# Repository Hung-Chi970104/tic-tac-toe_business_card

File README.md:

# Tic-Tac-Toe Business Card

**A playable RP2040 business card with a printed NFC antenna and a minimax computer opponent.**

[PCB layout](#pcb-layout) · [NFC design](#passive-nfc-and-antenna) · [Demos](#see-it-work) · [Schematic](#schematic) · [Design files](#design-files)

## PCB layout

The layout combines a large copper-coil NFC antenna with the game interface and embedded electronics. The **18 game LEDs form nine dual-colour cells**, giving each player one indicator per square; Next and Select buttons provide the controls.

## What I built

- Designed the RP2040 board, LED interface, USB-C connection and passive NFC circuit.
- Integrated a **25 × 48 mm PCB copper-coil antenna** with an **NT3H2111 NFC tag**.
- Implemented two-player gameplay and a **minimax opponent with alpha-beta pruning**, which skips search branches that cannot improve the chosen move.
- Completed two PCB revisions, resolving the initial NFC fault and demonstrating both gameplay and tap-to-open linking.

## Passive NFC and antenna

The coil is part of the PCB copper, connected to the NFC tag's antenna terminals. A compatible phone supplies the field needed for passive **13.56 MHz** NFC reading, so the portfolio link can be read **without USB power**. Gameplay uses the powered RP2040 and LED circuit.

The grid uses 18 LEDs; three additional indicators sit outside the nine game cells.

## See it work

| Demonstration | Watch |
|---|---|
| Two-player game | [Gameplay video](https://youtube.com/shorts/xTpW4rk7Zjw) |
| Computer opponent | [Minimax gameplay](https://youtu.be/wkJYNbXEyfI) |
| Passive NFC | [Phone tap → portfolio link](https://youtube.com/shorts/Xky8sBx_JWE) |

## Schematic

[Full-resolution schematic](assets/schematic.svg) · [KiCad schematic](Tic-tac-toe_Business_Card.kicad_sch)

## 3D views

Original board renders:

| Front | Back |
|---|---|
|  |  |

## Design files

| Resource | Link |
|---|---|
| KiCad project | [Project file](Tic-tac-toe_Business_Card.kicad_pro) |
| Routed board | [PCB source](Tic-tac-toe_Business_Card.kicad_pcb) |
| Copper layers | [Front](assets/Tic-tac-toe_Business_Card-F_Cu.svg) · [Back](assets/Tic-tac-toe_Business_Card-B_Cu.svg) |
| NFC footprint | [25 × 48 mm antenna source](lib/NFC_Tic_Tac_Toe.pretty/25X48MM_NFC_ANTENNA.kicad_mod) |
| Manufacturing exports | [Production files](production/) |

The repository contains the hardware design and demonstration assets. The gameplay implementation is demonstrated in the videos; a complete firmware release is not currently included here.

Designed and built by Hung-Chi Wang.

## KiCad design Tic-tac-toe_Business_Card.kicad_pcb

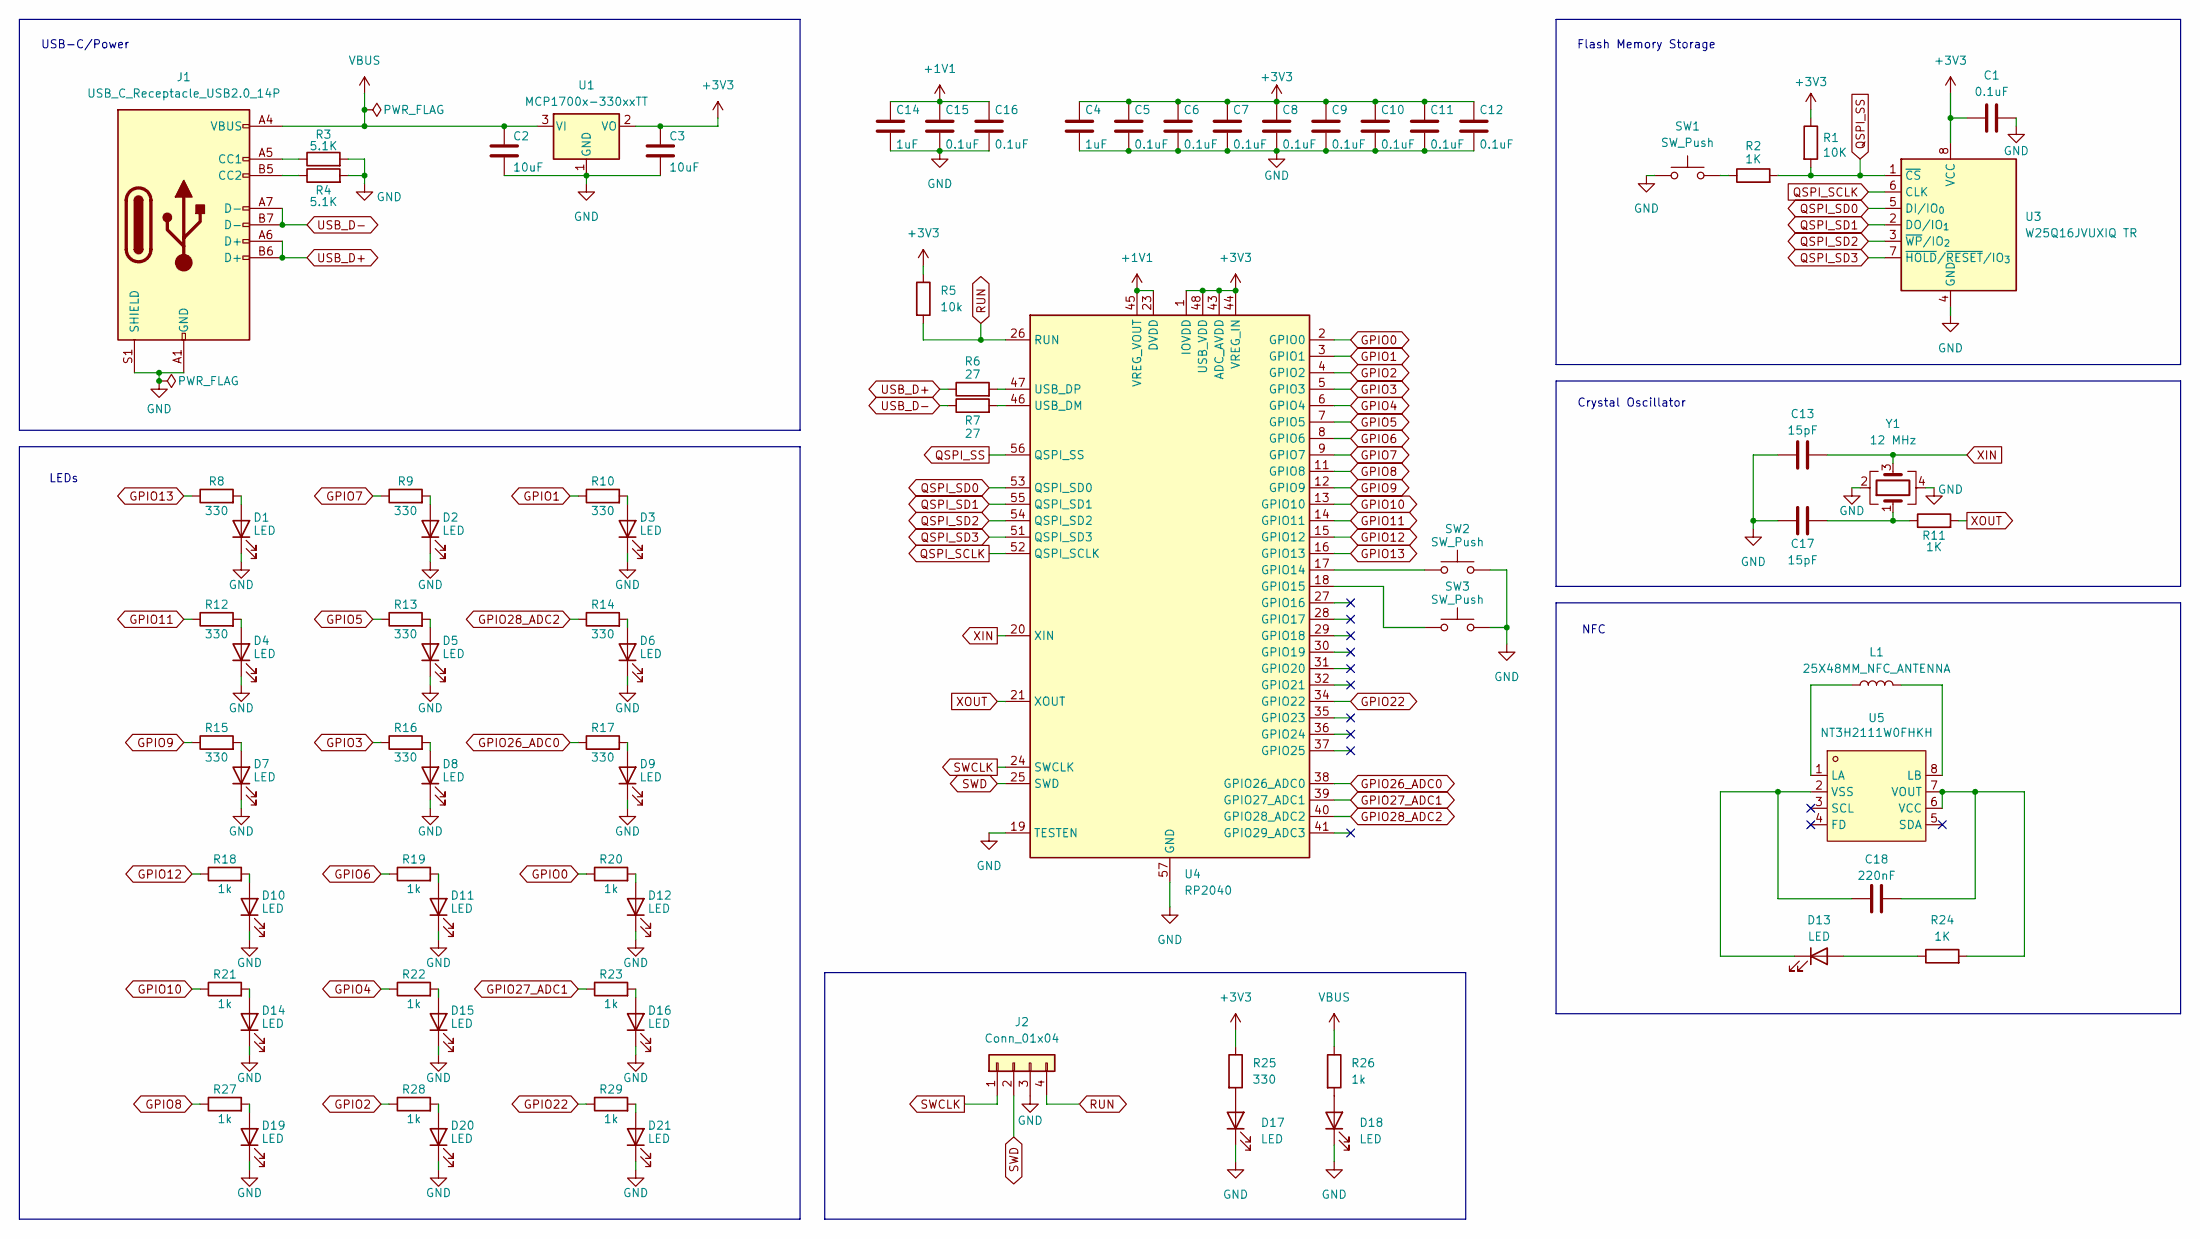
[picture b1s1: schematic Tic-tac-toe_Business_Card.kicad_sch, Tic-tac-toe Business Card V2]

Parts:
C1, C5, C6, C7, C8, C9, C10, C11, C12, C15, C16: 0.1uF; C_0402_1005Metric
C2, C3: 10uF; C_0603_1608Metric
C4, C14: 1uF; C_0402_1005Metric
C13, C17: 15pF; C_0402_1005Metric
C18: 220nF; C_0603_1608Metric
D1, D2, D3, D4, D5, D6, D7, D8, D9, D10, D11, D12, D14, D15, D16, D19, D20, D21: LED; LED_0805_2012Metric
D13: LED; LED_0402_1005Metric
D17, D18: LED; LED_0603_1608Metric
J1: USB_C_Receptacle_USB2.0_14P; USB_C_Receptacle_HRO_TYPE-C-31-M-12
J2: Conn_01x04; PinHeader_1x04_P2.54mm_Vertical
L1: 25X48MM_NFC_ANTENNA
R1: 10K; R_0402_1005Metric
R2, R11: 1K; R_0402_1005Metric
R3, R4: 5.1K; R_0402_1005Metric
R5: 10k; R_0402_1005Metric
R6, R7: 27; R_0402_1005Metric
R8, R9, R10, R12, R13, R14, R15, R16, R17: 330; R_0805_2012Metric
R18, R19, R20, R21, R22, R23, R27, R28, R29: 1k; R_0805_2012Metric
R24: 1K; R_0402_1005Metric; LCSC C23182
R25: 330; R_0402_1005Metric
R26: 1k; R_0402_1005Metric
SW1: SW_Push; SW_Push_SPST_NO_Alps_SKRK
SW2, SW3: SW_Push; SW_SPST_SKQG_WithoutStem
U1: MCP1700x-330xxTT; SOT-23
U3: W25Q16JVUXIQ TR; Winbond_USON-8-1EP_3x2mm_P0.5mm_EP0.2x1.6mm
U4: RP2040; QFN-56-1EP_7x7mm_P0.4mm_EP3.2x3.2mm
U5: NT3H2111W0FHKH; XQFN-8_L1.6-W1.6-P0.50-BL_NT3H2111W0FHKH; LCSC C710403
Y1: 12 MHz; Crystal_SMD_3225-4Pin_3.2x2.5mm

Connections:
+1V1: C14.1, C15.1, C16.1, U4.23 (DVDD), U4.45 (VREG_VOUT), U4.50 (DVDD)
+3V3: C1.1, C3.1, C4.1, C5.1, C6.1, C7.1, C8.1, C9.1, C10.1, C11.1, C12.1, R1.1, R5.1, R25.1, U1.2 (VO), U3.8 (VCC), U4.1 (IOVDD), U4.10 (IOVDD), U4.22 (IOVDD), U4.33 (IOVDD), U4.42 (IOVDD), U4.43 (ADC_AVDD), U4.44 (VREG_IN), U4.48 (USB_VDD), U4.49 (IOVDD)
GND: C1.2, C2.2, C3.2, C4.2, C5.2, C6.2, C7.2, C8.2, C9.2, C10.2, C11.2, C12.2, C13.1, C14.2, C15.2, C16.2, C17.1, D1.1 (K), D2.1 (K), D3.1 (K), D4.1 (K), D5.1 (K), D6.1 (K), D7.1 (K), D8.1 (K), D9.1 (K), D10.1 (K), D11.1 (K), D12.1 (K), D14.1 (K), D15.1 (K), D16.1 (K), D17.1 (K), D18.1 (K), D19.1 (K), D20.1 (K), D21.1 (K), J1.A1 (GND), J1.A12 (GND), J1.B1 (GND), J1.B12 (GND), J1.S1 (SHIELD), J2.3, R3.2, R4.2, SW1.1, SW2.2, SW3.2, U1.1 (GND), U3.4 (GND), U4.19 (TESTEN), U4.57 (GND), Y1.2, Y1.4
GPIO0: R20.1, U4.2 (GPIO0)
GPIO1: R10.1, U4.3 (GPIO1)
GPIO2: R28.1, U4.4 (GPIO2)
GPIO3: R16.1, U4.5 (GPIO3)
GPIO4: R22.1, U4.6 (GPIO4)
GPIO5: R13.1, U4.7 (GPIO5)
GPIO6: R19.1, U4.8 (GPIO6)
GPIO7: R9.1, U4.9 (GPIO7)
GPIO8: R27.1, U4.11 (GPIO8)
GPIO9: R15.1, U4.12 (GPIO9)
GPIO10: R21.1, U4.13 (GPIO10)
GPIO11: R12.1, U4.14 (GPIO11)
GPIO12: R18.1, U4.15 (GPIO12)
GPIO13: R8.1, U4.16 (GPIO13)
GPIO22: R29.1, U4.34 (GPIO22)
GPIO26_ADC0: R17.1, U4.38 (GPIO26_ADC0)
GPIO27_ADC1: R23.1, U4.39 (GPIO27_ADC1)
GPIO28_ADC2: R14.1, U4.40 (GPIO28_ADC2)
unnamed: C17.2, R11.1, Y1.1
unnamed: D1.2 (A), R8.2
unnamed: D2.2 (A), R9.2
unnamed: D3.2 (A), R10.2
unnamed: D4.2 (A), R12.2
unnamed: D5.2 (A), R13.2
unnamed: D6.2 (A), R14.2
unnamed: D7.2 (A), R15.2
unnamed: D8.2 (A), R16.2
unnamed: D9.2 (A), R17.2
unnamed: D10.2 (A), R18.2
unnamed: D11.2 (A), R19.2
unnamed: D12.2 (A), R20.2
unnamed: D13.2 (A), R24.1
unnamed: C18.1, D13.1 (K), U5.2 (VSS)
unnamed: D14.2 (A), R21.2
unnamed: D15.2 (A), R22.2
unnamed: D16.2 (A), R23.2
unnamed: D17.2 (A), R25.2
unnamed: D18.2 (A), R26.2
unnamed: D19.2 (A), R27.2
unnamed: D20.2 (A), R28.2
unnamed: D21.2 (A), R29.2
unnamed: J1.A5 (CC1), R3.1
unnamed: J1.B5 (CC2), R4.1
unnamed: R2.1, SW1.2
unnamed: SW2.1, U4.17 (GPIO14)
unnamed: SW3.1, U4.18 (GPIO15)
unnamed: R7.2, U4.46 (USB_DM)
unnamed: R6.2, U4.47 (USB_DP)
unnamed: L1.1, U5.1 (LA)
unnamed: L1.2, U5.8 (LB)
unnamed: C18.2, R24.2, U5.6 (VCC), U5.7 (VOUT)
QSPI_SCLK: U3.6 (CLK), U4.52 (QSPI_SCLK)
QSPI_SD0: U3.5 (DI/IO_{0}), U4.53 (QSPI_SD0)
QSPI_SD1: U3.2 (DO/IO_{1}), U4.55 (QSPI_SD1)
QSPI_SD2: U3.3 (~WP/IO_{2}), U4.54 (QSPI_SD2)
QSPI_SD3: U3.7 (~HOLD/~RESET/IO_{3}), U4.51 (QSPI_SD3)
QSPI_SS: R1.2, R2.2, U3.1 (~CS), U4.56 (QSPI_SS)
RUN: J2.4, R5.2, U4.26 (RUN)
SWCLK: J2.1, U4.24 (SWCLK)
SWD: J2.2, U4.25 (SWD)
USB_D+: J1.A6 (D+), J1.B6 (D+), R6.1
USB_D-: J1.A7 (D-), J1.B7 (D-), R7.1
VBUS: C2.1, J1.A4 (VBUS), J1.A9 (VBUS), J1.B4 (VBUS), J1.B9 (VBUS), R26.1, U1.3 (VI)
XIN: C13.2, U4.20 (XIN), Y1.3
XOUT: R11.2, U4.21 (XOUT)

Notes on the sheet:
NFC
Crystal Oscillator
LEDs
USB-C/Power
Flash Memory Storage

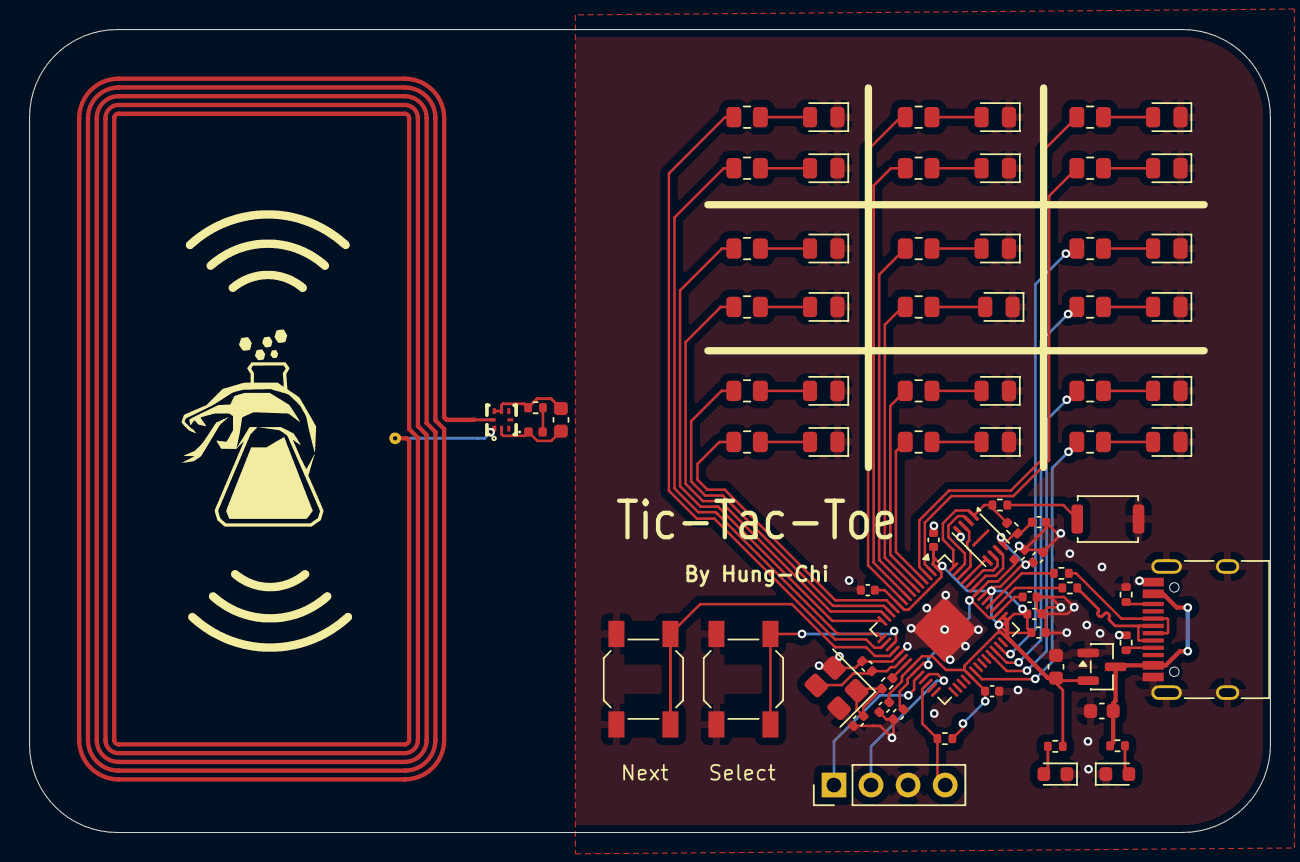
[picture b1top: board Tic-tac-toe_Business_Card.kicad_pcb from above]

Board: 2 copper layers, 85.0 x 55.0 mm, 77 parts (0 on the bottom side), 68 nets.

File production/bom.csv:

Designator,Footprint,Quantity,Value,LCSC Part #
"C1, C11, C12, C15, C16, C6, C7, C8, C9",0402,9,0.1uF,
"C13, C17",0402,2,15pF,
"C14, C4",0402,2,1uF,
C18,0603,1,220nF,
"C2, C3",0603,2,10uF,
"D1, D10, D11, D12, D14, D15, D16, D19, D2, D20, D21, D3, D4, D5, D6, D7, D8, D9",0805,18,LED,
D13,0402,1,LED,
"D17, D18",0603,2,LED,
J1,USB_C_Receptacle_HRO_TYPE-C-31-M-12,1,USB_C_Receptacle_USB2.0_14P,
J2,PinHeader_1x04_P2.54mm_Vertical,1,Conn_01x04,
L1,25X48MM_NFC_ANTENNA,1,25X48MM_NFC_ANTENNA,
"R1, R5",0402,2,10K,
"R10, R12, R13, R14, R15, R16, R17, R8, R9",0805,9,330,
"R11, R2, R26, R24",0402,4,1K,
"R18, R19, R20, R21, R22, R23, R27, R28, R29",0805,9,1k,
R25,0402,1,330,
"R3, R4",0402,2,5.1K,
"R6, R7",0402,2,27,
SW1,SW_Push_SPST_NO_Alps_SKRK,1,SW_Push,
"SW2, SW3",SW_SPST_SKQG_WithoutStem,2,SW_Push,
U1,SOT-23,1,MCP1700x-330xxTT,
U3,Winbond_USON-8-1EP_3x2mm_P0.5mm_EP0.2x1.6mm,1,W25Q16JVUXIQ TR,
U4,QFN-56-1EP_7x7mm_P0.4mm_EP3.2x3.2mm,1,RP2040,
U5,XQFN-8_L1.6-W1.6-P0.50-BL_NT3H2111W0FHKH,1,NT3H2111W0FHKH,C710403
Y1,Crystal_SMD_3225-4Pin_3.2x2.5mm,1,12 MHz,

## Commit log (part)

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2026-02-01 Finished coding gamee logic
2026-02-01 Update images
2026-04-03 Update Repo
